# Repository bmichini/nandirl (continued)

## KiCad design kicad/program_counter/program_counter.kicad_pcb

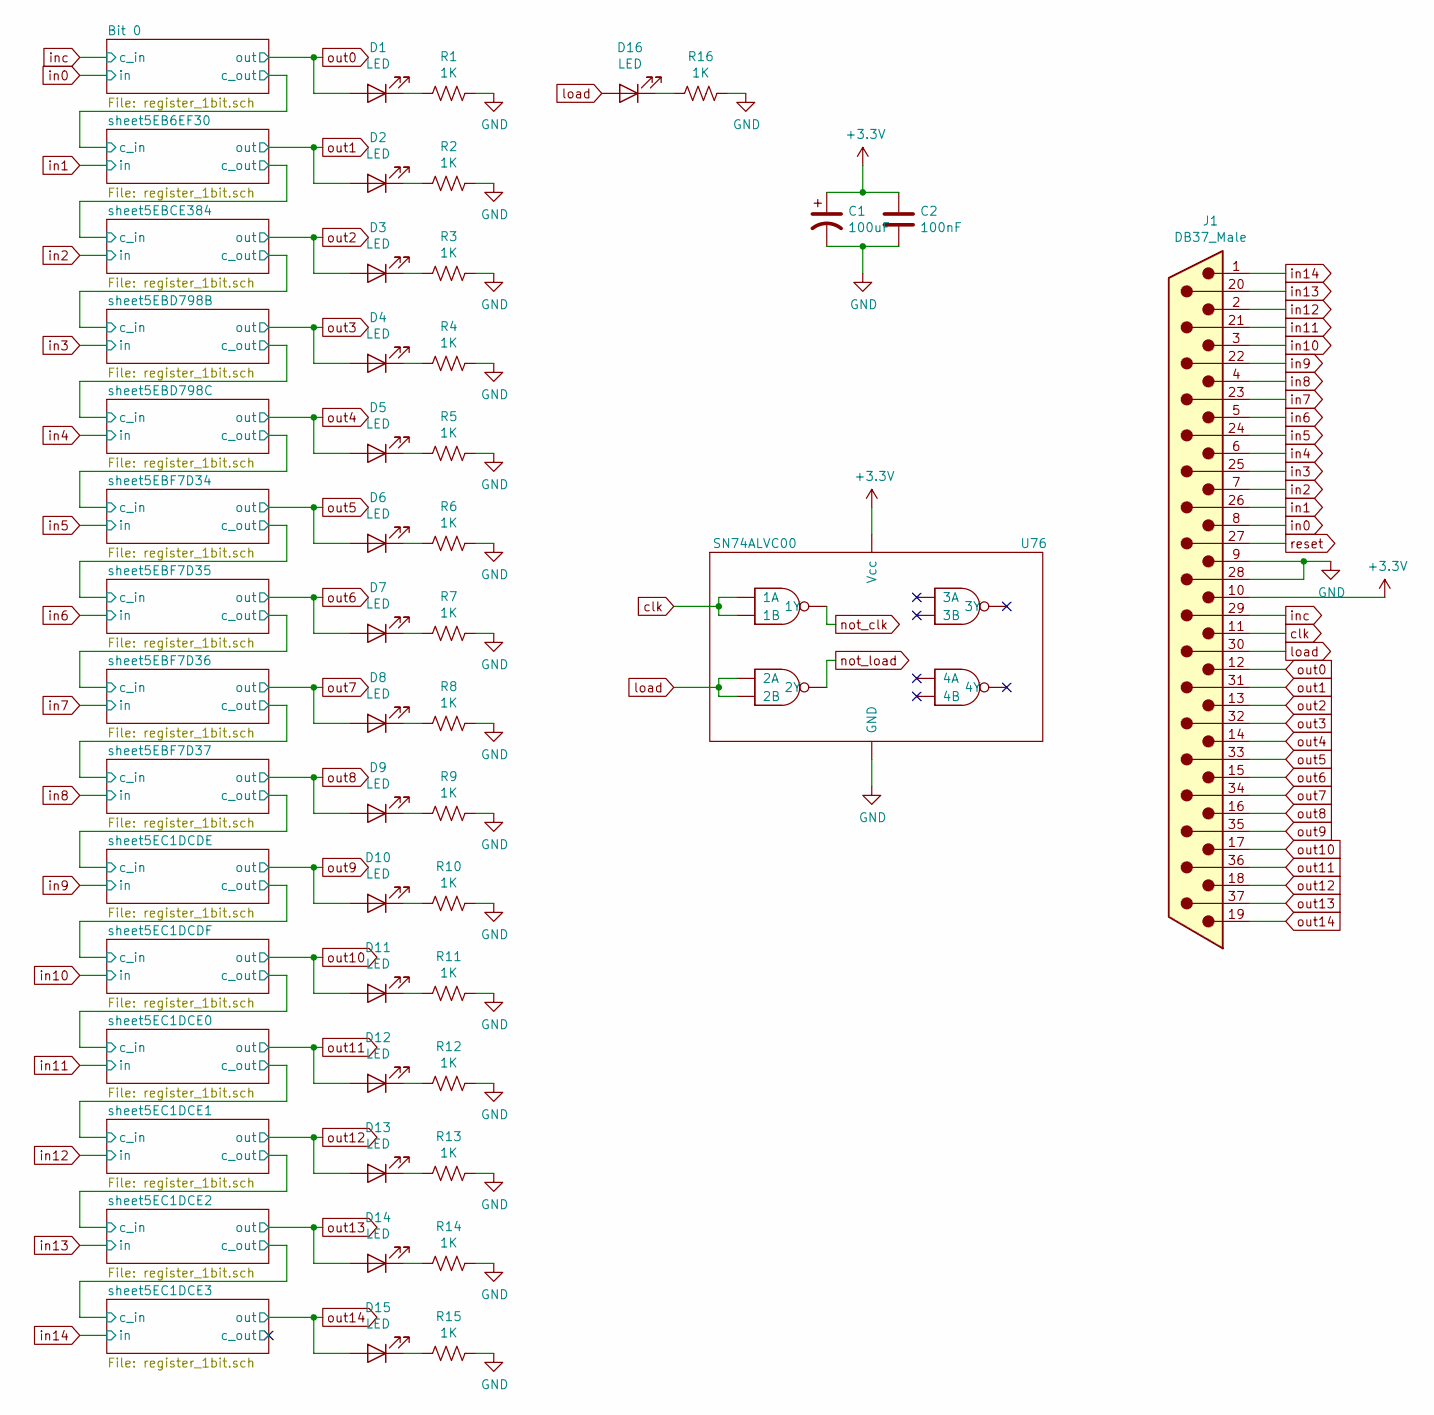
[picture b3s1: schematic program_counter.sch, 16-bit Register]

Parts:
C1: 100uF; CP_Radial_D8.0mm_P2.50mm; Digikey PN P15797CT-ND
C2: 100nF; C_Disc_D5.0mm_W2.5mm_P5.00mm; Digikey PN BC5229CT-ND
D1, D2, D3, D4, D5, D6, D7, D8, D9, D10, D11, D12, D13, D14, D15, D16: LED; LED_D5.0mm
J1: DB37_Male; DSUB-37_Male_Horizontal_P2.77x2.84mm_EdgePinOffset7.70mm_Ho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; Digikey PN AE10986-ND
R1, R2, R3, R4, R5, R6, R7, R8, R9, R10, R11, R12, R13, R14, R15, R16: 1K; R_1206_3216Metric; Digikey PN P1.0KECT-ND
U76: SN74ALVC00; TSSOP-14_4.4x5mm_P0.65mm; Digikey PN 296-5104-1-ND

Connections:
GND: C1.2, C2.2, J1.9, J1.28, R1.1, R2.1, R3.1, R4.1, R5.1, R6.1, R7.1, R8.1, R9.1, R10.1, R11.1, R12.1, R13.1, R14.1, R15.1, R16.1, U76.7 (GND); also elsewhere on the board
unnamed: D1.1 (K), R1.2
unnamed: D2.1 (K), R2.2
unnamed: D3.1 (K), R3.2
unnamed: D4.1 (K), R4.2
unnamed: D5.1 (K), R5.2
unnamed: D6.1 (K), R6.2
unnamed: D7.1 (K), R7.2
unnamed: D8.1 (K), R8.2
unnamed: D9.1 (K), R9.2
unnamed: D10.1 (K), R10.2
unnamed: D11.1 (K), R11.2
unnamed: D12.1 (K), R12.2
unnamed: D13.1 (K), R13.2
unnamed: D14.1 (K), R14.2
unnamed: D15.1 (K), R15.2
unnamed: D16.1 (K), R16.2
clk: J1.11, U76.1 (1A), U76.2 (1B); also elsewhere on the board
in0: J1.8; also elsewhere on the board
in1: J1.26; also elsewhere on the board
in2: J1.7; also elsewhere on the board
in3: J1.25; also elsewhere on the board
in4: J1.6; also elsewhere on the board
in5: J1.24; also elsewhere on the board
in6: J1.5; also elsewhere on the board
in7: J1.23; also elsewhere on the board
in8: J1.4; also elsewhere on the board
in9: J1.22; also elsewhere on the board
in10: J1.3; also elsewhere on the board
in11: J1.21; also elsewhere on the board
in12: J1.2; also elsewhere on the board
in13: J1.20; also elsewhere on the board
in14: J1.1; also elsewhere on the board
inc: J1.29; also elsewhere on the board
load: D16.2 (A), J1.30, U76.4 (2A), U76.5 (2B); also elsewhere on the board
not_clk: U76.3 (1Y); also elsewhere on the board
not_load: U76.6 (2Y); also elsewhere on the board
out0: D1.2 (A), J1.12; also elsewhere on the board
out1: D2.2 (A), J1.31; also elsewhere on the board
out2: D3.2 (A), J1.13; also elsewhere on the board
out3: D4.2 (A), J1.32; also elsewhere on the board
out4: D5.2 (A), J1.14; also elsewhere on the board
out5: D6.2 (A), J1.33; also elsewhere on the board
out6: D7.2 (A), J1.15; also elsewhere on the board
out7: D8.2 (A), J1.34; also elsewhere on the board
out8: D9.2 (A), J1.16; also elsewhere on the board
out9: D10.2 (A), J1.35; also elsewhere on the board
out10: D11.2 (A), J1.17; also elsewhere on the board
out11: D12.2 (A), J1.36; also elsewhere on the board
out12: D13.2 (A), J1.18; also elsewhere on the board
out13: D14.2 (A), J1.37; also elsewhere on the board
out14: D15.2 (A), J1.19; also elsewhere on the board
reset: J1.27; also elsewhere on the board

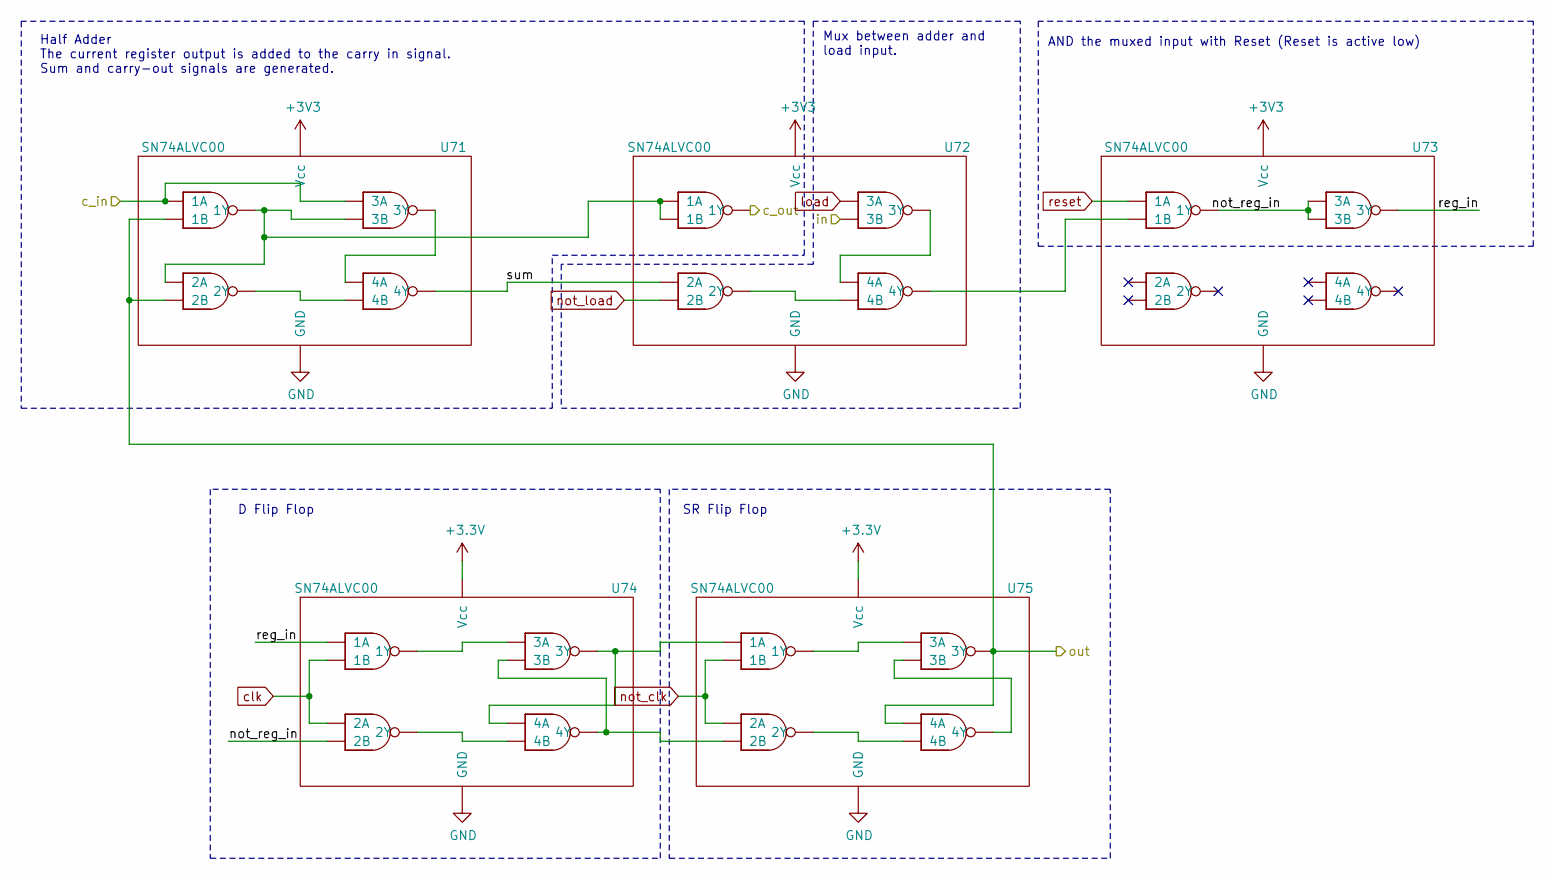
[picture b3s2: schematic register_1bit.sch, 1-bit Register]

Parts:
U1, U2, U3, U4, U5: SN74ALVC00; TSSOP-14_4.4x5mm_P0.65mm

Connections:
/Bit 0/not_reg_in: U3.3 (1Y), U3.9 (3A), U3.10 (3B), U4.5 (2B)
/Bit 0/reg_in: U3.8 (3Y), U4.1 (1A)
/Bit 0/sum: U1.11 (4Y), U2.4 (2A)
/sheet5EB6EF30/c_in: U2.3 (1Y); also elsewhere on the board
GND: U1.7 (GND), U2.7 (GND), U3.7 (GND), U4.7 (GND), U5.7 (GND); also elsewhere on the board
unnamed: U1.3 (1Y), U1.4 (2A), U1.10 (3B), U2.1 (1A), U2.2 (1B)
unnamed: U1.8 (3Y), U1.12 (4A)
unnamed: U1.6 (2Y), U1.13 (4B)
unnamed: U2.11 (4Y), U3.2 (1B)
unnamed: U2.8 (3Y), U2.12 (4A)
unnamed: U2.6 (2Y), U2.13 (4B)
unnamed: U4.3 (1Y), U4.9 (3A)
unnamed: U4.10 (3B), U4.11 (4Y), U5.5 (2B)
unnamed: U4.8 (3Y), U4.12 (4A), U5.1 (1A)
unnamed: U4.6 (2Y), U4.13 (4B)
unnamed: U5.3 (1Y), U5.9 (3A)
unnamed: U5.10 (3B), U5.11 (4Y)
unnamed: U5.6 (2Y), U5.13 (4B)
clk: U4.2 (1B), U4.4 (2A); also elsewhere on the board
in0: U2.10 (3B); also elsewhere on the board
inc: U1.1 (1A), U1.9 (3A); also elsewhere on the board
load: U2.9 (3A); also elsewhere on the board
not_clk: U5.2 (1B), U5.4 (2A); also elsewhere on the board
not_load: U2.5 (2B); also elsewhere on the board
out0: U1.2 (1B), U1.5 (2B), U5.8 (3Y), U5.12 (4A); also elsewhere on the board
reset: U3.1 (1A); also elsewhere on the board

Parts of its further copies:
U6, U7, U8, U9, U10, U11, U12, U13, U14, U15, U16, U17, U18, U19, U20, U21, U22, U23, U24, U25, U26, U27, U28, U29, U30, U31, U32, U33, U34, U35, U36, U37, U38, U39, U40, U41, U42, U43, U44, U45, U46, U47, U48, U49, U50, U51, U52, U53, U54, U55, U56, U57, U58, U59, U60, U61, U62, U63, U64, U65, U66, U67, U68, U69, U70, U71, U72, U73, U74, U75: SN74ALVC00; TSSOP-14_4.4x5mm_P0.65mm

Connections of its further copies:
/sheet5EB6EF30/c_in: U71.1 (1A), U71.9 (3A); also elsewhere on the board
/sheet5EB6EF30/not_reg_in: U73.3 (1Y), U73.9 (3A), U73.10 (3B), U74.5 (2B)
/sheet5EB6EF30/reg_in: U73.8 (3Y), U74.1 (1A)
/sheet5EB6EF30/sum: U71.11 (4Y), U72.4 (2A)
/sheet5EBCE384/c_in: U66.1 (1A), U66.9 (3A), U72.3 (1Y)
/sheet5EBCE384/not_reg_in: U68.3 (1Y), U68.9 (3A), U68.10 (3B), U69.5 (2B)
/sheet5EBCE384/reg_in: U68.8 (3Y), U69.1 (1A)
/sheet5EBCE384/sum: U66.11 (4Y), U67.4 (2A)
/sheet5EBD798B/c_in: U61.1 (1A), U61.9 (3A), U67.3 (1Y)
/sheet5EBD798B/not_reg_in: U63.3 (1Y), U63.9 (3A), U63.10 (3B), U64.5 (2B)
/sheet5EBD798B/reg_in: U63.8 (3Y), U64.1 (1A)
/sheet5EBD798B/sum: U61.11 (4Y), U62.4 (2A)
/sheet5EBD798C/c_in: U56.1 (1A), U56.9 (3A), U62.3 (1Y)
/sheet5EBD798C/not_reg_in: U58.3 (1Y), U58.9 (3A), U58.10 (3B), U59.5 (2B)
/sheet5EBD798C/reg_in: U58.8 (3Y), U59.1 (1A)
/sheet5EBD798C/sum: U56.11 (4Y), U57.4 (2A)
/sheet5EBF7D34/c_in: U51.1 (1A), U51.9 (3A), U57.3 (1Y)
/sheet5EBF7D34/not_reg_in: U53.3 (1Y), U53.9 (3A), U53.10 (3B), U54.5 (2B)
/sheet5EBF7D34/reg_in: U53.8 (3Y), U54.1 (1A)
/sheet5EBF7D34/sum: U51.11 (4Y), U52.4 (2A)
/sheet5EBF7D35/c_in: U46.1 (1A), U46.9 (3A), U52.3 (1Y)
/sheet5EBF7D35/not_reg_in: U48.3 (1Y), U48.9 (3A), U48.10 (3B), U49.5 (2B)
/sheet5EBF7D35/reg_in: U48.8 (3Y), U49.1 (1A)
/sheet5EBF7D35/sum: U46.11 (4Y), U47.4 (2A)
/sheet5EBF7D36/c_in: U41.1 (1A), U41.9 (3A), U47.3 (1Y)
/sheet5EBF7D36/not_reg_in: U43.3 (1Y), U43.9 (3A), U43.10 (3B), U44.5 (2B)
/sheet5EBF7D36/reg_in: U43.8 (3Y), U44.1 (1A)
/sheet5EBF7D36/sum: U41.11 (4Y), U42.4 (2A)
/sheet5EBF7D37/c_in: U36.1 (1A), U36.9 (3A), U42.3 (1Y)
/sheet5EBF7D37/not_reg_in: U38.3 (1Y), U38.9 (3A), U38.10 (3B), U39.5 (2B)
/sheet5EBF7D37/reg_in: U38.8 (3Y), U39.1 (1A)
/sheet5EBF7D37/sum: U36.11 (4Y), U37.4 (2A)
/sheet5EC1DCDE/c_in: U31.1 (1A), U31.9 (3A), U37.3 (1Y)
/sheet5EC1DCDE/not_reg_in: U33.3 (1Y), U33.9 (3A), U33.10 (3B), U34.5 (2B)
/sheet5EC1DCDE/reg_in: U33.8 (3Y), U34.1 (1A)
/sheet5EC1DCDE/sum: U31.11 (4Y), U32.4 (2A)
/sheet5EC1DCDF/c_in: U26.1 (1A), U26.9 (3A), U32.3 (1Y)
/sheet5EC1DCDF/not_reg_in: U28.3 (1Y), U28.9 (3A), U28.10 (3B), U29.5 (2B)
/sheet5EC1DCDF/reg_in: U28.8 (3Y), U29.1 (1A)
/sheet5EC1DCDF/sum: U26.11 (4Y), U27.4 (2A)
/sheet5EC1DCE0/c_in: U21.1 (1A), U21.9 (3A), U27.3 (1Y)
/sheet5EC1DCE0/not_reg_in: U23.3 (1Y), U23.9 (3A), U23.10 (3B), U24.5 (2B)
/sheet5EC1DCE0/reg_in: U23.8 (3Y), U24.1 (1A)
/sheet5EC1DCE0/sum: U21.11 (4Y), U22.4 (2A)
/sheet5EC1DCE1/c_in: U16.1 (1A), U16.9 (3A), U22.3 (1Y)
/sheet5EC1DCE1/not_reg_in: U18.3 (1Y), U18.9 (3A), U18.10 (3B), U19.5 (2B)
/sheet5EC1DCE1/reg_in: U18.8 (3Y), U19.1 (1A)
/sheet5EC1DCE1/sum: U16.11 (4Y), U17.4 (2A)
/sheet5EC1DCE2/c_in: U11.1 (1A), U11.9 (3A), U17.3 (1Y)
/sheet5EC1DCE2/not_reg_in: U13.3 (1Y), U13.9 (3A), U13.10 (3B), U14.5 (2B)
/sheet5EC1DCE2/reg_in: U13.8 (3Y), U14.1 (1A)
/sheet5EC1DCE2/sum: U11.11 (4Y), U12.4 (2A)
/sheet5EC1DCE3/c_in: U6.1 (1A), U6.9 (3A), U12.3 (1Y)
/sheet5EC1DCE3/c_out: U7.3 (1Y)
/sheet5EC1DCE3/not_reg_in: U8.3 (1Y), U8.9 (3A), U8.10 (3B), U9.5 (2B)
/sheet5EC1DCE3/reg_in: U8.8 (3Y), U9.1 (1A)
/sheet5EC1DCE3/sum: U6.11 (4Y), U7.4 (2A)
GND: U6.7 (GND), U7.7 (GND), U8.7 (GND), U9.7 (GND), U10.7 (GND), U11.7 (GND), U12.7 (GND), U13.7 (GND), U14.7 (GND), U15.7 (GND), U16.7 (GND), U17.7 (GND), U18.7 (GND), U19.7 (GND), U20.7 (GND), U21.7 (GND), U22.7 (GND), U23.7 (GND), U24.7 (GND), U25.7 (GND), U26.7 (GND), U27.7 (GND), U28.7 (GND), U29.7 (GND), U30.7 (GND), U31.7 (GND), U32.7 (GND), U33.7 (GND), U34.7 (GND), U35.7 (GND), U36.7 (GND), U37.7 (GND), U38.7 (GND), U39.7 (GND), U40.7 (GND), U41.7 (GND), U42.7 (GND), U43.7 (GND), U44.7 (GND), U45.7 (GND), U46.7 (GND), U47.7 (GND), U48.7 (GND), U49.7 (GND), U50.7 (GND), U51.7 (GND), U52.7 (GND), U53.7 (GND), U54.7 (GND), U55.7 (GND), U56.7 (GND), U57.7 (GND), U58.7 (GND), U59.7 (GND), U60.7 (GND), U61.7 (GND), U62.7 (GND), U63.7 (GND), U64.7 (GND), U65.7 (GND), U66.7 (GND), U67.7 (GND), U68.7 (GND), U69.7 (GND), U70.7 (GND), U71.7 (GND), U72.7 (GND), U73.7 (GND), U74.7 (GND), U75.7 (GND); also elsewhere on the board
unnamed: U6.3 (1Y), U6.4 (2A), U6.10 (3B), U7.1 (1A), U7.2 (1B)
unnamed: U6.8 (3Y), U6.12 (4A)
unnamed: U6.6 (2Y), U6.13 (4B)
unnamed: U7.11 (4Y), U8.2 (1B)
unnamed: U7.8 (3Y), U7.12 (4A)
unnamed: U7.6 (2Y), U7.13 (4B)
unnamed: U9.3 (1Y), U9.9 (3A)
unnamed: U9.6 (2Y), U9.13 (4B)
unnamed: U9.8 (3Y), U9.12 (4A), U10.1 (1A)
unnamed: U10.3 (1Y), U10.9 (3A)
unnamed: U9.10 (3B), U9.11 (4Y), U10.5 (2B)
unnamed: U10.10 (3B), U10.11 (4Y)
unnamed: U10.6 (2Y), U10.13 (4B)
unnamed: U11.3 (1Y), U11.4 (2A), U11.10 (3B), U12.1 (1A), U12.2 (1B)
unnamed: U11.8 (3Y), U11.12 (4A)
unnamed: U11.6 (2Y), U11.13 (4B)
unnamed: U12.11 (4Y), U13.2 (1B)
unnamed: U12.8 (3Y), U12.12 (4A)
unnamed: U12.6 (2Y), U12.13 (4B)
unnamed: U14.3 (1Y), U14.9 (3A)
unnamed: U14.10 (3B), U14.11 (4Y), U15.5 (2B)
unnamed: U14.8 (3Y), U14.12 (4A), U15.1 (1A)
unnamed: U14.6 (2Y), U14.13 (4B)
unnamed: U15.3 (1Y), U15.9 (3A)
unnamed: U15.10 (3B), U15.11 (4Y)
unnamed: U15.6 (2Y), U15.13 (4B)
unnamed: U16.3 (1Y), U16.4 (2A), U16.10 (3B), U17.1 (1A), U17.2 (1B)
unnamed: U16.8 (3Y), U16.12 (4A)
unnamed: U16.6 (2Y), U16.13 (4B)
unnamed: U17.11 (4Y), U18.2 (1B)
unnamed: U17.8 (3Y), U17.12 (4A)
unnamed: U17.6 (2Y), U17.13 (4B)
unnamed: U19.3 (1Y), U19.9 (3A)
unnamed: U19.10 (3B), U19.11 (4Y), U20.5 (2B)
unnamed: U19.8 (3Y), U19.12 (4A), U20.1 (1A)
unnamed: U19.6 (2Y), U19.13 (4B)
unnamed: U20.3 (1Y), U20.9 (3A)
unnamed: U20.10 (3B), U20.11 (4Y)
unnamed: U20.6 (2Y), U20.13 (4B)
unnamed: U21.3 (1Y), U21.4 (2A), U21.10 (3B), U22.1 (1A), U22.2 (1B)
unnamed: U21.8 (3Y), U21.12 (4A)
unnamed: U21.6 (2Y), U21.13 (4B)
unnamed: U22.11 (4Y), U23.2 (1B)
unnamed: U22.8 (3Y), U22.12 (4A)
unnamed: U22.6 (2Y), U22.13 (4B)
unnamed: U24.3 (1Y), U24.9 (3A)
unnamed: U24.10 (3B), U24.11 (4Y), U25.5 (2B)
unnamed: U24.8 (3Y), U24.12 (4A), U25.1 (1A)
unnamed: U24.6 (2Y), U24.13 (4B)
unnamed: U25.3 (1Y), U25.9 (3A)
unnamed: U25.10 (3B), U25.11 (4Y)
unnamed: U25.6 (2Y), U25.13 (4B)
unnamed: U26.3 (1Y), U26.4 (2A), U26.10 (3B), U27.1 (1A), U27.2 (1B)
unnamed: U26.8 (3Y), U26.12 (4A)
unnamed: U26.6 (2Y), U26.13 (4B)
unnamed: U27.11 (4Y), U28.2 (1B)
unnamed: U27.8 (3Y), U27.12 (4A)
unnamed: U27.6 (2Y), U27.13 (4B)
unnamed: U29.3 (1Y), U29.9 (3A)
unnamed: U29.10 (3B), U29.11 (4Y), U30.5 (2B)
unnamed: U29.8 (3Y), U29.12 (4A), U30.1 (1A)
unnamed: U29.6 (2Y), U29.13 (4B)
unnamed: U30.3 (1Y), U30.9 (3A)
unnamed: U30.10 (3B), U30.11 (4Y)
unnamed: U30.6 (2Y), U30.13 (4B)
unnamed: U31.3 (1Y), U31.4 (2A), U31.10 (3B), U32.1 (1A), U32.2 (1B)
unnamed: U31.8 (3Y), U31.12 (4A)
unnamed: U31.6 (2Y), U31.13 (4B)
unnamed: U32.11 (4Y), U33.2 (1B)
unnamed: U32.8 (3Y), U32.12 (4A)
unnamed: U32.6 (2Y), U32.13 (4B)
unnamed: U34.3 (1Y), U34.9 (3A)
unnamed: U34.10 (3B), U34.11 (4Y), U35.5 (2B)
unnamed: U34.8 (3Y), U34.12 (4A), U35.1 (1A)
unnamed: U34.6 (2Y), U34.13 (4B)
unnamed: U35.3 (1Y), U35.9 (3A)
unnamed: U35.10 (3B), U35.11 (4Y)
unnamed: U35.6 (2Y), U35.13 (4B)
unnamed: U36.3 (1Y), U36.4 (2A), U36.10 (3B), U37.1 (1A), U37.2 (1B)
unnamed: U36.8 (3Y), U36.12 (4A)
unnamed: U36.6 (2Y), U36.13 (4B)
unnamed: U37.11 (4Y), U38.2 (1B)
unnamed: U37.8 (3Y), U37.12 (4A)
unnamed: U37.6 (2Y), U37.13 (4B)
unnamed: U39.3 (1Y), U39.9 (3A)
unnamed: U39.10 (3B), U39.11 (4Y), U40.5 (2B)
unnamed: U39.8 (3Y), U39.12 (4A), U40.1 (1A)
unnamed: U39.6 (2Y), U39.13 (4B)
unnamed: U40.3 (1Y), U40.9 (3A)
unnamed: U40.10 (3B), U40.11 (4Y)
unnamed: U40.6 (2Y), U40.13 (4B)
unnamed: U41.3 (1Y), U41.4 (2A), U41.10 (3B), U42.1 (1A), U42.2 (1B)
unnamed: U41.8 (3Y), U41.12 (4A)
unnamed: U41.6 (2Y), U41.13 (4B)
unnamed: U42.11 (4Y), U43.2 (1B)
unnamed: U42.8 (3Y), U42.12 (4A)
unnamed: U42.6 (2Y), U42.13 (4B)
unnamed: U44.3 (1Y), U44.9 (3A)
unnamed: U44.10 (3B), U44.11 (4Y), U45.5 (2B)
unnamed: U44.8 (3Y), U44.12 (4A), U45.1 (1A)
unnamed: U44.6 (2Y), U44.13 (4B)
unnamed: U45.3 (1Y), U45.9 (3A)
unnamed: U45.10 (3B), U45.11 (4Y)
unnamed: U45.6 (2Y), U45.13 (4B)
unnamed: U46.3 (1Y), U46.4 (2A), U46.10 (3B), U47.1 (1A), U47.2 (1B)
unnamed: U46.8 (3Y), U46.12 (4A)
unnamed: U46.6 (2Y), U46.13 (4B)
unnamed: U47.11 (4Y), U48.2 (1B)
unnamed: U47.8 (3Y), U47.12 (4A)
unnamed: U47.6 (2Y), U47.13 (4B)
unnamed: U49.3 (1Y), U49.9 (3A)
unnamed: U49.10 (3B), U49.11 (4Y), U50.5 (2B)
unnamed: U49.8 (3Y), U49.12 (4A), U50.1 (1A)
unnamed: U49.6 (2Y), U49.13 (4B)
unnamed: U50.3 (1Y), U50.9 (3A)
unnamed: U50.10 (3B), U50.11 (4Y)
unnamed: U50.6 (2Y), U50.13 (4B)
unnamed: U51.3 (1Y), U51.4 (2A), U51.10 (3B), U52.1 (1A), U52.2 (1B)
unnamed: U51.8 (3Y), U51.12 (4A)
unnamed: U51.6 (2Y), U51.13 (4B)
unnamed: U52.11 (4Y), U53.2 (1B)
unnamed: U52.8 (3Y), U52.12 (4A)
unnamed: U52.6 (2Y), U52.13 (4B)
unnamed: U54.3 (1Y), U54.9 (3A)
unnamed: U54.10 (3B), U54.11 (4Y), U55.5 (2B)
unnamed: U54.8 (3Y), U54.12 (4A), U55.1 (1A)
unnamed: U54.6 (2Y), U54.13 (4B)
unnamed: U55.3 (1Y), U55.9 (3A)
unnamed: U55.10 (3B), U55.11 (4Y)
unnamed: U55.6 (2Y), U55.13 (4B)
unnamed: U56.3 (1Y), U56.4 (2A), U56.10 (3B), U57.1 (1A), U57.2 (1B)
unnamed: U56.8 (3Y), U56.12 (4A)
unnamed: U56.6 (2Y), U56.13 (4B)
unnamed: U57.11 (4Y), U58.2 (1B)
unnamed: U57.8 (3Y), U57.12 (4A)
unnamed: U57.6 (2Y), U57.13 (4B)
unnamed: U59.3 (1Y), U59.9 (3A)
unnamed: U59.10 (3B), U59.11 (4Y), U60.5 (2B)
unnamed: U59.8 (3Y), U59.12 (4A), U60.1 (1A)
unnamed: U59.6 (2Y), U59.13 (4B)
unnamed: U60.3 (1Y), U60.9 (3A)
unnamed: U60.10 (3B), U60.11 (4Y)
unnamed: U60.6 (2Y), U60.13 (4B)
unnamed: U61.3 (1Y), U61.4 (2A), U61.10 (3B), U62.1 (1A), U62.2 (1B)
unnamed: U61.8 (3Y), U61.12 (4A)
unnamed: U61.6 (2Y), U61.13 (4B)
unnamed: U62.11 (4Y), U63.2 (1B)
unnamed: U62.8 (3Y), U62.12 (4A)
unnamed: U62.6 (2Y), U62.13 (4B)
unnamed: U64.3 (1Y), U64.9 (3A)
unnamed: U64.10 (3B), U64.11 (4Y), U65.5 (2B)
unnamed: U64.8 (3Y), U64.12 (4A), U65.1 (1A)
unnamed: U64.6 (2Y), U64.13 (4B)
unnamed: U65.3 (1Y), U65.9 (3A)
unnamed: U65.10 (3B), U65.11 (4Y)
unnamed: U65.6 (2Y), U65.13 (4B)
unnamed: U66.3 (1Y), U66.4 (2A), U66.10 (3B), U67.1 (1A), U67.2 (1B)
unnamed: U66.8 (3Y), U66.12 (4A)
unnamed: U66.6 (2Y), U66.13 (4B)
unnamed: U67.11 (4Y), U68.2 (1B)
unnamed: U67.8 (3Y), U67.12 (4A)
unnamed: U67.6 (2Y), U67.13 (4B)
unnamed: U69.3 (1Y), U69.9 (3A)
unnamed: U69.10 (3B), U69.11 (4Y), U70.5 (2B)
unnamed: U69.8 (3Y), U69.12 (4A), U70.1 (1A)
unnamed: U69.6 (2Y), U69.13 (4B)
unnamed: U70.3 (1Y), U70.9 (3A)
unnamed: U70.10 (3B), U70.11 (4Y)
unnamed: U70.6 (2Y), U70.13 (4B)
unnamed: U71.3 (1Y), U71.4 (2A), U71.10 (3B), U72.1 (1A), U72.2 (1B)
unnamed: U71.8 (3Y), U71.12 (4A)
unnamed: U71.6 (2Y), U71.13 (4B)
unnamed: U72.11 (4Y), U73.2 (1B)
unnamed: U72.8 (3Y), U72.12 (4A)
unnamed: U72.6 (2Y), U72.13 (4B)
unnamed: U74.3 (1Y), U74.9 (3A)
unnamed: U74.10 (3B), U74.11 (4Y), U75.5 (2B)
unnamed: U74.8 (3Y), U74.12 (4A), U75.1 (1A)
unnamed: U74.6 (2Y), U74.13 (4B)
unnamed: U75.3 (1Y), U75.9 (3A)
unnamed: U75.10 (3B), U75.11 (4Y)
unnamed: U75.6 (2Y), U75.13 (4B)
clk: U9.2 (1B), U9.4 (2A), U14.2 (1B), U14.4 (2A), U19.2 (1B), U19.4 (2A), U24.2 (1B), U24.4 (2A), U29.2 (1B), U29.4 (2A), U34.2 (1B), U34.4 (2A), U39.2 (1B), U39.4 (2A), U44.2 (1B), U44.4 (2A), U49.2 (1B), U49.4 (2A), U54.2 (1B), U54.4 (2A), U59.2 (1B), U59.4 (2A), U64.2 (1B), U64.4 (2A), U69.2 (1B), U69.4 (2A), U74.2 (1B), U74.4 (2A); also elsewhere on the board
in1: U72.10 (3B); also elsewhere on the board
in2: U67.10 (3B); also elsewhere on the board
in3: U62.10 (3B); also elsewhere on the board
in4: U57.10 (3B); also elsewhere on the board
in5: U52.10 (3B); also elsewhere on the board
in6: U47.10 (3B); also elsewhere on the board
in7: U42.10 (3B); also elsewhere on the board
in8: U37.10 (3B); also elsewhere on the board
in9: U32.10 (3B); also elsewhere on the board
in10: U27.10 (3B); also elsewhere on the board
in11: U22.10 (3B); also elsewhere on the board
in12: U17.10 (3B); also elsewhere on the board
in13: U12.10 (3B); also elsewhere on the board
in14: U7.10 (3B); also elsewhere on the board
load: U7.9 (3A), U12.9 (3A), U17.9 (3A), U22.9 (3A), U27.9 (3A), U32.9 (3A), U37.9 (3A), U42.9 (3A), U47.9 (3A), U52.9 (3A), U57.9 (3A), U62.9 (3A), U67.9 (3A), U72.9 (3A); also elsewhere on the board
not_clk: U10.2 (1B), U10.4 (2A), U15.2 (1B), U15.4 (2A), U20.2 (1B), U20.4 (2A), U25.2 (1B), U25.4 (2A), U30.2 (1B), U30.4 (2A), U35.2 (1B), U35.4 (2A), U40.2 (1B), U40.4 (2A), U45.2 (1B), U45.4 (2A), U50.2 (1B), U50.4 (2A), U55.2 (1B), U55.4 (2A), U60.2 (1B), U60.4 (2A), U65.2 (1B), U65.4 (2A), U70.2 (1B), U70.4 (2A), U75.2 (1B), U75.4 (2A); also elsewhere on the board
not_load: U7.5 (2B), U12.5 (2B), U17.5 (2B), U22.5 (2B), U27.5 (2B), U32.5 (2B), U37.5 (2B), U42.5 (2B), U47.5 (2B), U52.5 (2B), U57.5 (2B), U62.5 (2B), U67.5 (2B), U72.5 (2B); also elsewhere on the board
out1: U71.2 (1B), U71.5 (2B), U75.8 (3Y), U75.12 (4A); also elsewhere on the board
out2: U66.2 (1B), U66.5 (2B), U70.8 (3Y), U70.12 (4A); also elsewhere on the board
out3: U61.2 (1B), U61.5 (2B), U65.8 (3Y), U65.12 (4A); also elsewhere on the board
out4: U56.2 (1B), U56.5 (2B), U60.8 (3Y), U60.12 (4A); also elsewhere on the board
out5: U51.2 (1B), U51.5 (2B), U55.8 (3Y), U55.12 (4A); also elsewhere on the board
out6: U46.2 (1B), U46.5 (2B), U50.8 (3Y), U50.12 (4A); also elsewhere on the board
out7: U41.2 (1B), U41.5 (2B), U45.8 (3Y), U45.12 (4A); also elsewhere on the board
out8: U36.2 (1B), U36.5 (2B), U40.8 (3Y), U40.12 (4A); also elsewhere on the board
out9: U31.2 (1B), U31.5 (2B), U35.8 (3Y), U35.12 (4A); also elsewhere on the board
out10: U26.2 (1B), U26.5 (2B), U30.8 (3Y), U30.12 (4A); also elsewhere on the board
out11: U21.2 (1B), U21.5 (2B), U25.8 (3Y), U25.12 (4A); also elsewhere on the board
out12: U16.2 (1B), U16.5 (2B), U20.8 (3Y), U20.12 (4A); also elsewhere on the board
out13: U11.2 (1B), U11.5 (2B), U15.8 (3Y), U15.12 (4A); also elsewhere on the board
out14: U6.2 (1B), U6.5 (2B), U10.8 (3Y), U10.12 (4A); also elsewhere on the board
reset: U8.1 (1A), U13.1 (1A), U18.1 (1A), U23.1 (1A), U28.1 (1A), U33.1 (1A), U38.1 (1A), U43.1 (1A), U48.1 (1A), U53.1 (1A), U58.1 (1A), U63.1 (1A), U68.1 (1A), U73.1 (1A); also elsewhere on the board

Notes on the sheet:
D Flip Flop
SR Flip Flop
Half Adder The current register output is added to the carry in signal. Sum and carry-out signals are generated.
Mux between adder and load input.
AND the muxed input with Reset (Reset is active low)

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
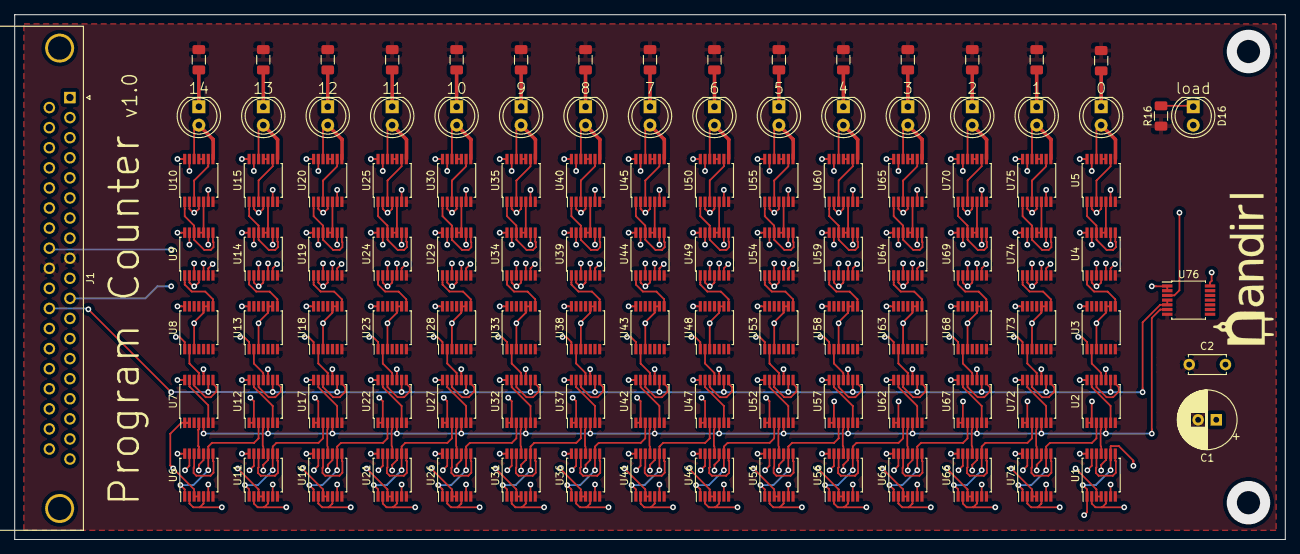
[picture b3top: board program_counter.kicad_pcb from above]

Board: 4 copper layers, 175.3 x 72.4 mm, 111 parts (0 on the bottom side), 308 nets.
